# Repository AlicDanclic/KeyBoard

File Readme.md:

<center><h1>客制化键盘 -- 主键盘部分</h1></center>

<hr style="border: none; height: 2px; background: linear-gradient(to right, #ff0000, #ff7f00, #ffff00, #00ff00, #0000ff, #4b0082, #8f00ff); width: 100%; margin: 0 auto;">
<div style="text-align: center; font-family: 'Times New Roman', serif; margin: 20px auto; max-width: 800px;">
    <div style="margin: 20px 0;">
    	
    </div>
    <div style="font-weight: bold; font-size: 18px; color: #333; margin: 10px 0;">
    	Copyright Statement
    </div>
    <div style="font-size: 14px; color: #666; margin: 5px 0; font-family: 'SimSun', 'Times New Roman', serif;">
    	本文档/代码/作品受版权保护，版权所有@EternoPax。保留所有权利。
    </div>
    <div style="font-size: 14px; color: #666; margin: 5px 0; font-family: 'SimSun', 'Times New Roman', serif;">
        未经允许请勿转载<br>
        Do not reproduce without permission
    </div>
    <div style="font-size: 14px; color: #666; margin: 5px 0; font-family: 'SimSun', 'Times New Roman', serif;">
        联系我👉EternoPax@outlook.con
    </div>
    <div style="display: flex; align-items: center; justify-content: center; margin: 5px 0;">
        <span style="font-size: 14px; color: #666; font-family: 'SimSun', 'Times New Roman', serif; margin-right: 10px;">
            @Copyright EternoPax
        </span>
        
    </div>
</div>
<hr style="border: none; height: 2px; background: linear-gradient(to right, #ff0000, #ff7f00, #ffff00, #00ff00, #0000ff, #4b0082, #8f00ff); width: 100%; margin: 0 auto;">

> 作为一个客制化键盘的主键盘,在这里我将介绍我的学习过程,希望一起学习

### 基础介绍

作为一个客制化键盘来说,最基础的部分有外壳,PCB,定位板,键轴和键帽,而其他多大都是辅助使用,有了这些东西就基本可以做出来一个客制化键盘了。

### 键盘布局

> [Keyboard Layout Editor](https://www.keyboard-layout-editor.com/?ref=producthunt#/)

这是通过网站设计的键盘布局,虽然这个网站的功能很多,当实际上用不到,笔者就简单介绍一下个人常用的几个功能.

在PreSet里面是我们常见的键盘布局,个人比较喜欢在ANSI104全键盘的基础上进行删减.

在当你选中其中的一个按键,上边的DeleteKeys会亮起,你可以直接使用Delete进行删除,也可以左键选中按下Delete一起删除(注意:选中会出现一个框,只有完全在框里的按键会被选中)

选中按键后可以按下方向键来调整位置

在

在Raw data里面是我们键盘的布局格式,这个是我们以后用来绘制CAD的数据

在右上角可以看到Download,请你再绘制好之后务必下载JSON和SVG,其中JSON是为了方便以后再进行layout的修改,而SVG是为了之后的键帽设计做准备.

### 原理图绘制

### PCB绘制

### 键帽设计

### 3D外壳

### 固件编写

### 最终成果

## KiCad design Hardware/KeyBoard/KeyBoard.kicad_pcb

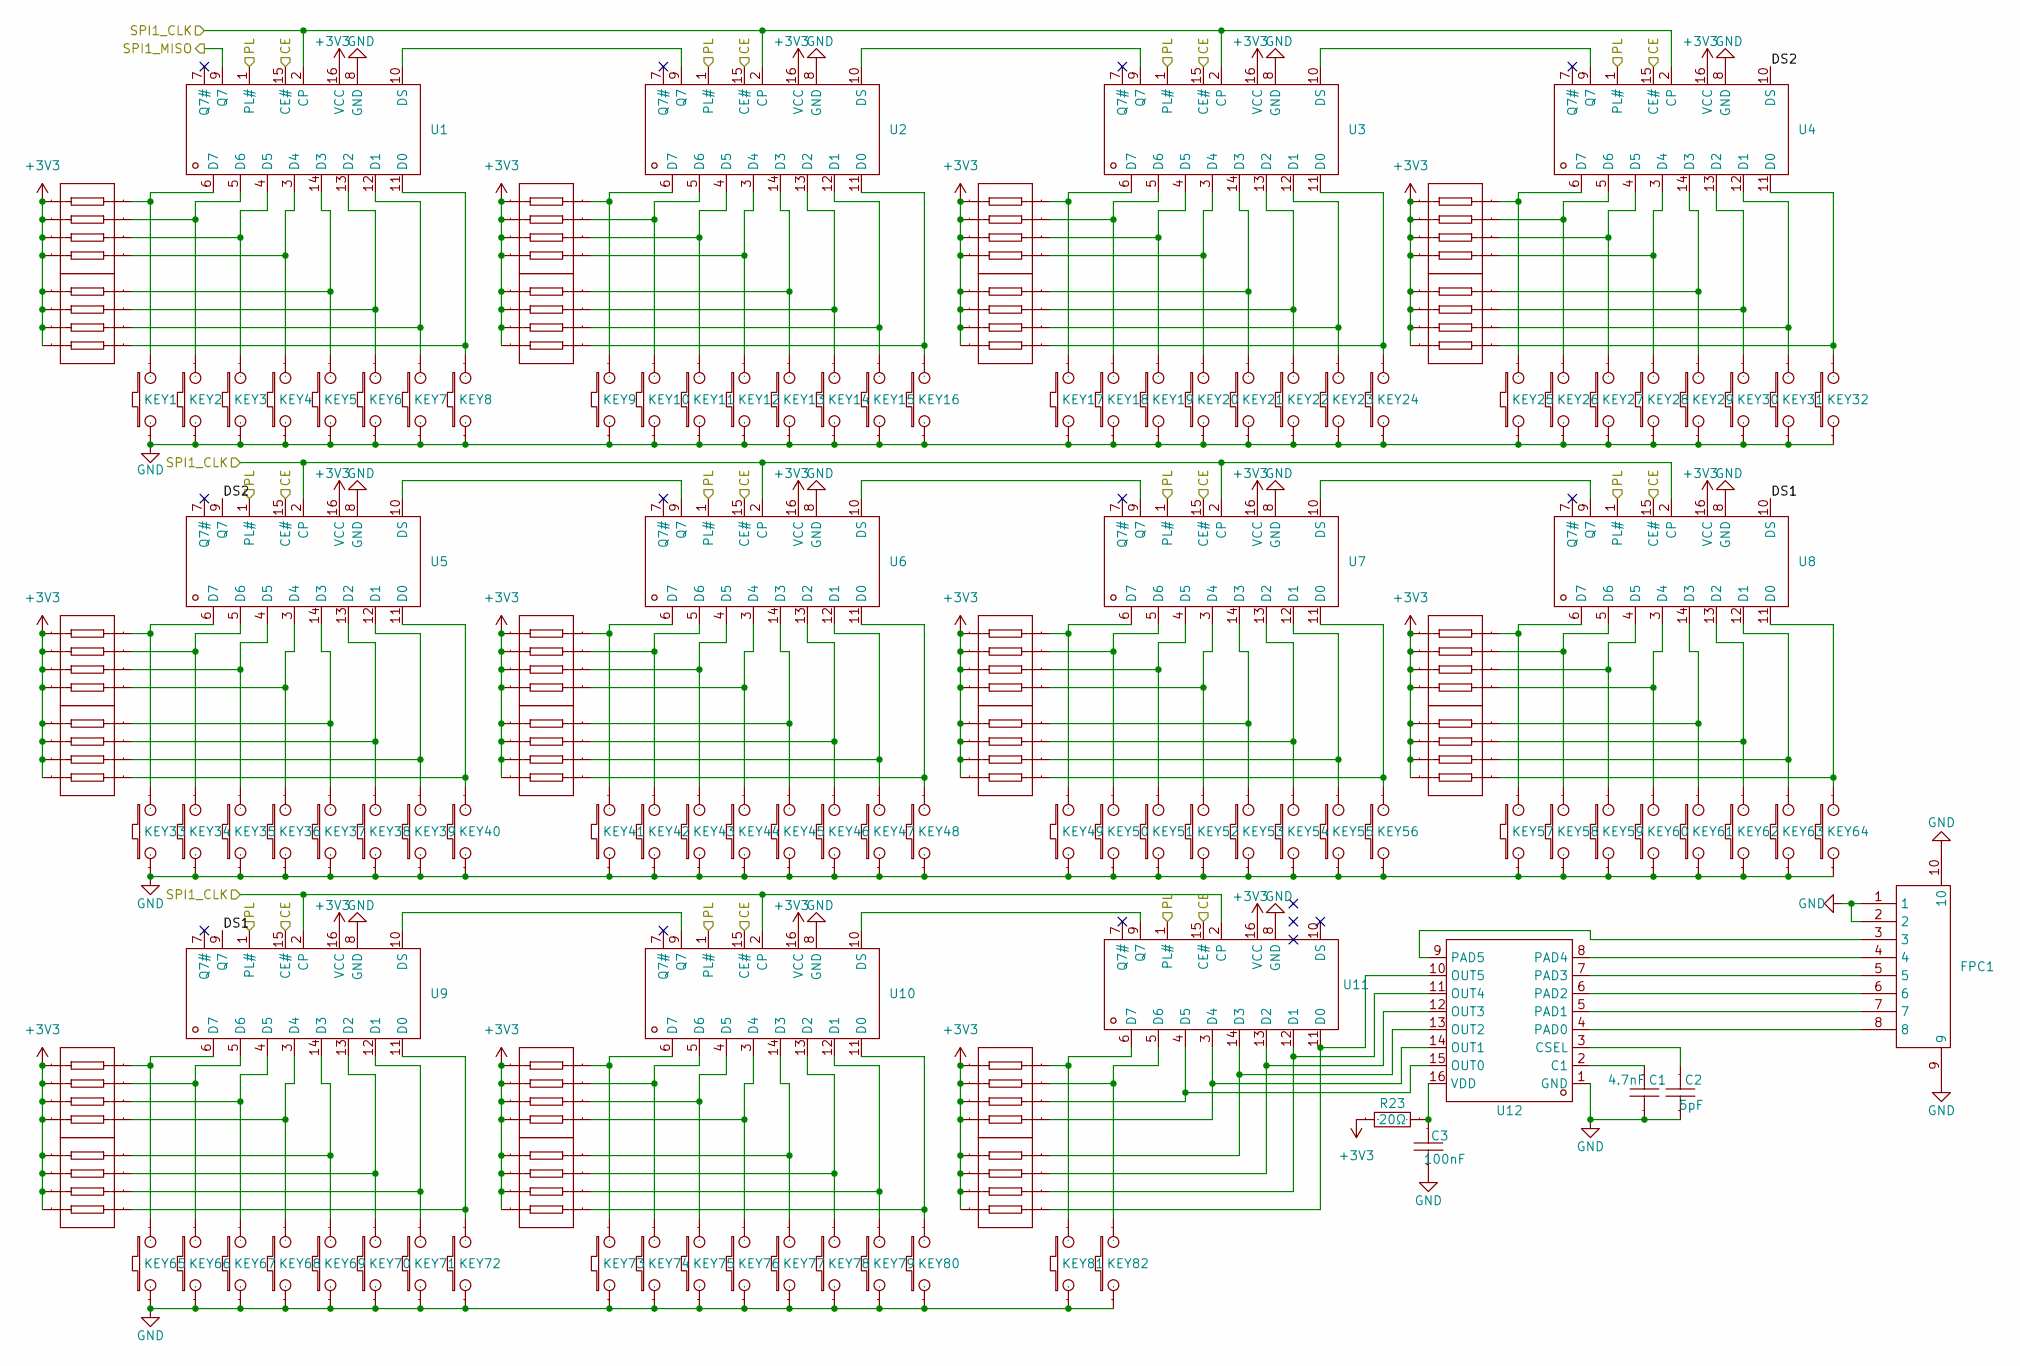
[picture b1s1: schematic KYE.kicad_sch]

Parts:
C1: 4.7nF; C0402; Manufacturer Part 0402B472K500NT; LCSC Part Name 4.7nF ±10% 50V
C2: 5pF; C0402; Manufacturer Part 0402B472K500NT; LCSC Part Name 4.7nF ±10% 50V
C3: 100nF; C0402; Manufacturer Part 0402B472K500NT; LCSC Part Name 4.7nF ±10% 50V
FPC1: FPC-SMD_P0.50-8P_FGS-XJ-H2.0; Manufacturer Part AFC01-S08FCA-00; LCSC Part Name 0.5mm P数:8 翻盖式 下接
KEY1, KEY2, KEY3, KEY4, KEY5, KEY6, KEY7, KEY8, KEY9, KEY10, KEY11, KEY12, KEY13, KEY14, KEY15, KEY16, KEY17, KEY18, KEY19, KEY20, KEY21, KEY22, KEY23, KEY24, KEY25, KEY26, KEY27, KEY28, KEY29, KEY30, KEY31, KEY32, KEY33, KEY34, KEY35, KEY36, KEY37, KEY38, KEY39, KEY40, KEY41, KEY42, KEY43, KEY44, KEY45, KEY46, KEY47, KEY48, KEY49, KEY50, KEY51, KEY52, KEY53, KEY54, KEY55, KEY56, KEY57, KEY58, KEY59, KEY60, KEY61, KEY62, KEY63, KEY64, KEY65, KEY66, KEY67, KEY68, KEY69, KEY70, KEY71, KEY72, KEY73, KEY74, KEY75, KEY76, KEY77, KEY78, KEY79, KEY80, KEY81, KEY82: MX-KEY-INSTALLED
R1, R2, R3, R4, R5, R6, R7, R8, R9, R10, R11, R12, R13, R14, R15, R16, R17, R18, R19, R20, R21, R22: 10kΩ; RES-ARRAY-SMD_0603-8P-L3.2-W1.6-BL; Manufacturer Part 4D03WGJ0103T5E; LCSC Part Name 10kΩ ±5%
R23: 20Ω; R0402; Manufacturer Part 0402WGF220JTCE; LCSC Part Name 22Ω ±1% 62.5mW
U1, U2, U3, U4, U5, U6, U7, U8, U9, U10, U11: SOIC-16_L9.9-W3.9-P1.27-LS6.0-BL; Manufacturer Part 74HC165D,653; LCSC Part Name 74HC165D,653
U12: SOP-16_L10.0-W3.9-P1.27-LS6.0-BL; Manufacturer Part XW06A; LCSC Part Name XW06A

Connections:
+3V3: R1.5, R1.6, R1.7, R1.8, R2.5, R2.6, R2.7, R2.8, R3.5, R3.6, R3.7, R3.8, R4.5, R4.6, R4.7, R4.8, R5.5, R5.6, R5.7, R5.8, R6.5, R6.6, R6.7, R6.8, R7.5, R7.6, R7.7, R7.8, R8.5, R8.6, R8.7, R8.8, R9.5, R9.6, R9.7, R9.8, R10.5, R10.6, R10.7, R10.8, R11.5, R11.6, R11.7, R11.8, R12.5, R12.6, R12.7, R12.8, R13.5, R13.6, R13.7, R13.8, R14.5, R14.6, R14.7, R14.8, R15.5, R15.6, R15.7, R15.8, R16.5, R16.6, R16.7, R16.8, R17.5, R17.6, R17.7, R17.8, R18.5, R18.6, R18.7, R18.8, R19.5, R19.6, R19.7, R19.8, R20.5, R20.6, R20.7, R20.8, R21.5, R21.6, R21.7, R21.8, R22.5, R22.6, R22.7, R22.8, R23.1, U1.16 (VCC), U2.16 (VCC), U3.16 (VCC), U4.16 (VCC), U5.16 (VCC), U6.16 (VCC), U7.16 (VCC), U8.16 (VCC), U9.16 (VCC), U10.16 (VCC), U11.16 (VCC); also elsewhere on the board
/KEY/CE: U1.15 (CE#), U2.15 (CE#), U3.15 (CE#), U4.15 (CE#), U5.15 (CE#), U6.15 (CE#), U7.15 (CE#), U8.15 (CE#), U9.15 (CE#), U10.15 (CE#), U11.15 (CE#); also elsewhere on the board
/KEY/DS1: U8.10 (DS), U9.9 (Q7)
/KEY/DS2: U4.10 (DS), U5.9 (Q7)
/KEY/PL: U1.1 (PL#), U2.1 (PL#), U3.1 (PL#), U4.1 (PL#), U5.1 (PL#), U6.1 (PL#), U7.1 (PL#), U8.1 (PL#), U9.1 (PL#), U10.1 (PL#), U11.1 (PL#); also elsewhere on the board
/KEY/SPI1_CLK: U1.2 (CP), U2.2 (CP), U3.2 (CP), U4.2 (CP), U5.2 (CP), U6.2 (CP), U7.2 (CP), U8.2 (CP), U9.2 (CP), U10.2 (CP), U11.2 (CP); also elsewhere on the board
/KEY/SPI1_MISO: U1.9 (Q7); also elsewhere on the board
GND: C1.2, C2.1, C3.1, FPC1.1, FPC1.2, FPC1.9, FPC1.10, KEY1.1, KEY2.1, KEY3.1, KEY4.1, KEY5.1, KEY6.1, KEY7.1, KEY8.1, KEY9.1, KEY10.1, KEY11.1, KEY12.1, KEY13.1, KEY14.1, KEY15.1, KEY16.1, KEY17.1, KEY18.1, KEY19.1, KEY20.1, KEY21.1, KEY22.1, KEY23.1, KEY24.1, KEY25.1, KEY26.1, KEY27.1, KEY28.1, KEY29.1, KEY30.1, KEY31.1, KEY32.1, KEY33.1, KEY34.1, KEY35.1, KEY36.1, KEY37.1, KEY38.1, KEY39.1, KEY40.1, KEY41.1, KEY42.1, KEY43.1, KEY44.1, KEY45.1, KEY46.1, KEY47.1, KEY48.1, KEY49.1, KEY50.1, KEY51.1, KEY52.1, KEY53.1, KEY54.1, KEY55.1, KEY56.1, KEY57.1, KEY58.1, KEY59.1, KEY60.1, KEY61.1, KEY62.1, KEY63.1, KEY64.1, KEY65.1, KEY66.1, KEY67.1, KEY68.1, KEY69.1, KEY70.1, KEY71.1, KEY72.1, KEY73.1, KEY74.1, KEY75.1, KEY76.1, KEY77.1, KEY78.1, KEY79.1, KEY80.1, KEY81.1, KEY82.1, U1.8 (GND), U2.8 (GND), U3.8 (GND), U4.8 (GND), U5.8 (GND), U6.8 (GND), U7.8 (GND), U8.8 (GND), U9.8 (GND), U10.8 (GND), U11.8 (GND), U12.1 (GND); also elsewhere on the board
unnamed: KEY8.2, R2.4, U1.11 (D0)
unnamed: KEY7.2, R2.3, U1.12 (D1)
unnamed: KEY6.2, R2.2, U1.13 (D2)
unnamed: KEY5.2, R2.1, U1.14 (D3)
unnamed: KEY4.2, R1.4, U1.3 (D4)
unnamed: KEY3.2, R1.3, U1.4 (D5)
unnamed: KEY2.2, R1.2, U1.5 (D6)
unnamed: KEY1.2, R1.1, U1.6 (D7)
unnamed: U1.10 (DS), U2.9 (Q7)
unnamed: KEY16.2, R4.4, U2.11 (D0)
unnamed: KEY15.2, R4.3, U2.12 (D1)
unnamed: KEY14.2, R4.2, U2.13 (D2)
unnamed: KEY13.2, R4.1, U2.14 (D3)
unnamed: KEY12.2, R3.4, U2.3 (D4)
unnamed: KEY11.2, R3.3, U2.4 (D5)
unnamed: KEY10.2, R3.2, U2.5 (D6)
unnamed: KEY9.2, R3.1, U2.6 (D7)
unnamed: U2.10 (DS), U3.9 (Q7)
unnamed: KEY24.2, R6.4, U3.11 (D0)
unnamed: KEY23.2, R6.3, U3.12 (D1)
unnamed: KEY22.2, R6.2, U3.13 (D2)
unnamed: KEY21.2, R6.1, U3.14 (D3)
unnamed: KEY20.2, R5.4, U3.3 (D4)
unnamed: KEY19.2, R5.3, U3.4 (D5)
unnamed: KEY18.2, R5.2, U3.5 (D6)
unnamed: KEY17.2, R5.1, U3.6 (D7)
unnamed: U3.10 (DS), U4.9 (Q7)
unnamed: KEY32.2, R8.4, U4.11 (D0)
unnamed: KEY31.2, R8.3, U4.12 (D1)
unnamed: KEY30.2, R8.2, U4.13 (D2)
unnamed: KEY29.2, R8.1, U4.14 (D3)
unnamed: KEY28.2, R7.4, U4.3 (D4)
unnamed: KEY27.2, R7.3, U4.4 (D5)
unnamed: KEY26.2, R7.2, U4.5 (D6)
unnamed: KEY25.2, R7.1, U4.6 (D7)
unnamed: KEY40.2, R10.4, U5.11 (D0)
unnamed: KEY39.2, R10.3, U5.12 (D1)
unnamed: KEY38.2, R10.2, U5.13 (D2)
unnamed: KEY37.2, R10.1, U5.14 (D3)
unnamed: KEY36.2, R9.4, U5.3 (D4)
unnamed: KEY35.2, R9.3, U5.4 (D5)
unnamed: KEY34.2, R9.2, U5.5 (D6)
unnamed: KEY33.2, R9.1, U5.6 (D7)
unnamed: U5.10 (DS), U6.9 (Q7)
unnamed: KEY48.2, R12.4, U6.11 (D0)
unnamed: KEY47.2, R12.3, U6.12 (D1)
unnamed: KEY46.2, R12.2, U6.13 (D2)
unnamed: KEY45.2, R12.1, U6.14 (D3)
unnamed: KEY44.2, R11.4, U6.3 (D4)
unnamed: KEY43.2, R11.3, U6.4 (D5)
unnamed: KEY42.2, R11.2, U6.5 (D6)
unnamed: KEY41.2, R11.1, U6.6 (D7)
unnamed: U6.10 (DS), U7.9 (Q7)
unnamed: KEY56.2, R14.4, U7.11 (D0)
unnamed: KEY55.2, R14.3, U7.12 (D1)
unnamed: KEY54.2, R14.2, U7.13 (D2)
unnamed: KEY53.2, R14.1, U7.14 (D3)
unnamed: KEY52.2, R13.4, U7.3 (D4)
unnamed: KEY51.2, R13.3, U7.4 (D5)
unnamed: KEY50.2, R13.2, U7.5 (D6)
unnamed: KEY49.2, R13.1, U7.6 (D7)
unnamed: U7.10 (DS), U8.9 (Q7)
unnamed: KEY64.2, R16.4, U8.11 (D0)
unnamed: KEY63.2, R16.3, U8.12 (D1)
unnamed: KEY62.2, R16.2, U8.13 (D2)
unnamed: KEY61.2, R16.1, U8.14 (D3)
unnamed: KEY60.2, R15.4, U8.3 (D4)
unnamed: KEY59.2, R15.3, U8.4 (D5)
unnamed: KEY58.2, R15.2, U8.5 (D6)
unnamed: KEY57.2, R15.1, U8.6 (D7)
unnamed: KEY72.2, R18.4, U9.11 (D0)
unnamed: KEY71.2, R18.3, U9.12 (D1)
unnamed: KEY70.2, R18.2, U9.13 (D2)
unnamed: KEY69.2, R18.1, U9.14 (D3)
unnamed: KEY68.2, R17.4, U9.3 (D4)
unnamed: KEY67.2, R17.3, U9.4 (D5)
unnamed: KEY66.2, R17.2, U9.5 (D6)
unnamed: KEY65.2, R17.1, U9.6 (D7)
unnamed: KEY80.2, R20.4, U10.11 (D0)
unnamed: KEY79.2, R20.3, U10.12 (D1)
unnamed: KEY78.2, R20.2, U10.13 (D2)
unnamed: KEY77.2, R20.1, U10.14 (D3)
unnamed: KEY76.2, R19.4, U10.3 (D4)
unnamed: KEY75.2, R19.3, U10.4 (D5)
unnamed: KEY74.2, R19.2, U10.5 (D6)
unnamed: KEY73.2, R19.1, U10.6 (D7)
unnamed: U10.10 (DS), U11.9 (Q7)
unnamed: U9.10 (DS), U10.9 (Q7)
unnamed: R22.4, U11.11 (D0), U12.10 (OUT5)
unnamed: R22.3, U11.12 (D1), U12.11 (OUT4)
unnamed: R22.2, U11.13 (D2), U12.12 (OUT3)
unnamed: R22.1, U11.14 (D3), U12.13 (OUT2)
unnamed: R21.4, U11.3 (D4), U12.14 (OUT1)
unnamed: R21.3, U11.4 (D5), U12.15 (OUT0)
unnamed: KEY82.2, R21.2, U11.5 (D6)
unnamed: KEY81.2, R21.1, U11.6 (D7)
unnamed: C1.1, U12.2 (C1)
unnamed: C2.2, U12.3 (CSEL)
unnamed: FPC1.8, U12.4 (PAD0)
unnamed: FPC1.7, U12.5 (PAD1)
unnamed: FPC1.6, U12.6 (PAD2)
unnamed: FPC1.5, U12.7 (PAD3)
unnamed: FPC1.4, U12.8 (PAD4)
unnamed: FPC1.3, U12.9 (PAD5)
unnamed: C3.2, R23.2, U12.16 (VDD)

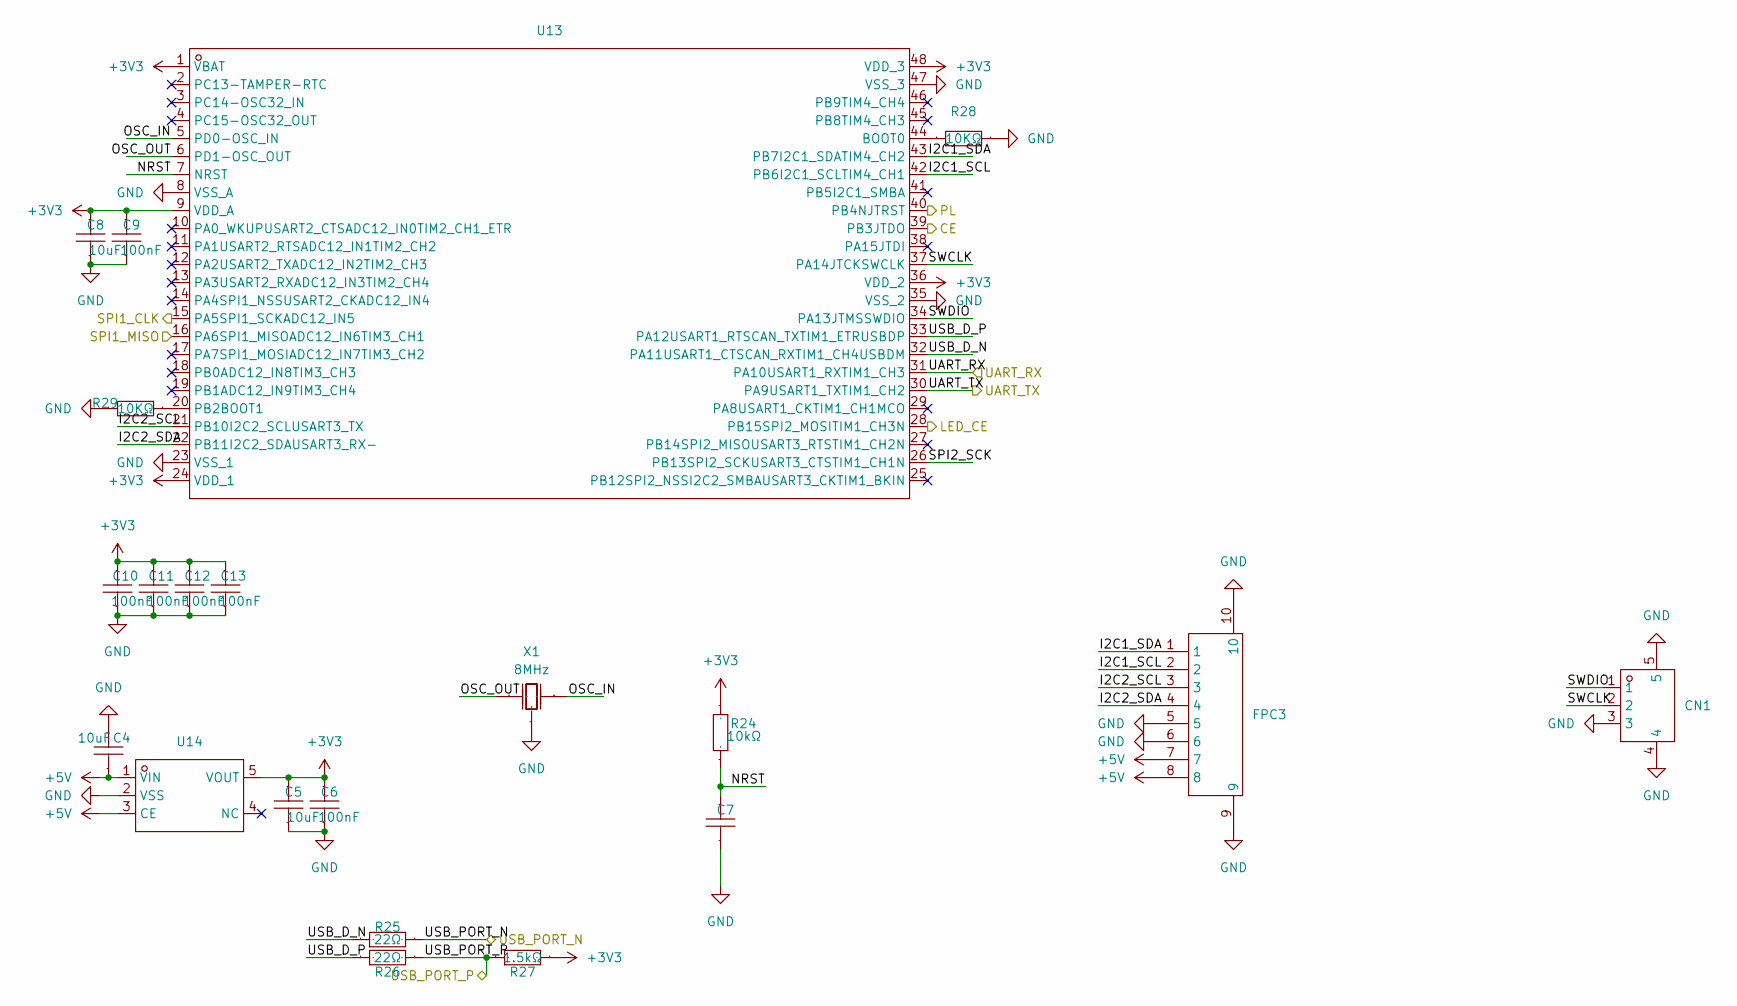
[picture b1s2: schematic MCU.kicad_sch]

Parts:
C4, C5, C8: 10uF; C0402; Manufacturer Part 0402B472K500NT; LCSC Part Name 4.7nF ±10% 50V
C6, C7, C9, C10, C11, C12, C13: 100nF; C0402; Manufacturer Part 0402B472K500NT; LCSC Part Name 4.7nF ±10% 50V
CN1: CONN-TH_3P-P1.25_GH1.25; Manufacturer Part WAFER-GH1.25-3PWB; LCSC Part Name 1x3P 间距:1.25mm 卧贴 系列:GH
FPC3: FPC-SMD_P0.50-8P_FGS-XJ-H2.0; Manufacturer Part AFC01-S08FCA-00; LCSC Part Name 0.5mm P数:8 翻盖式 下接
R24: 10kΩ; R0402; Manufacturer Part 0402WGF220JTCE; LCSC Part Name 22Ω ±1% 62.5mW
R25, R26: 22Ω; R0402; Manufacturer Part 0402WGF220JTCE; LCSC Part Name 22Ω ±1% 62.5mW
R27: 1.5kΩ; R0402; Manufacturer Part 0402WGF220JTCE; LCSC Part Name 22Ω ±1% 62.5mW
R28, R29: 10KΩ; R0402; Manufacturer Part 0402WGF220JTCE; LCSC Part Name 22Ω ±1% 62.5mW
U13: LQFP-48_L7.0-W7.0-P0.50-LS9.0-BL; Manufacturer Part STM32F103CBT6; LCSC Part Name STM32F103CBT6
U14: SOT-25_L3.0-W1.6-P0.95-LS2.8-BL; Manufacturer Part XC6210B332MR; LCSC Part Name Vin=6V Vout=3.3V 900mA 60dB@(1kHz)
X1: 8MHz; OSC-SMD_3P-L3.2-W1.3-P1.20; Manufacturer Part CSTNE8M00GH5C000R0; LCSC Part Name 8MHz ±0.07% 33pF

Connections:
+3V3: C5.1, C6.1, C8.1, C9.1, C10.1, C11.1, C12.1, C13.1, R24.2, R27.2, U13.1 (VBAT), U13.9 (VDD_A), U13.24 (VDD_1), U13.36 (VDD_2), U13.48 (VDD_3), U14.5 (VOUT); also elsewhere on the board
+5V: C4.1, FPC3.7, FPC3.8, U14.1 (VIN), U14.3 (CE); also elsewhere on the board
/Device/USB_1_DN: R25.2; also elsewhere on the board
/Device/USB_1_DP: R26.2, R27.1; also elsewhere on the board
/KEY/CE: U13.39 (PB3JTDO); also elsewhere on the board
/KEY/PL: U13.40 (PB4NJTRST); also elsewhere on the board
/KEY/SPI1_CLK: U13.15 (PA5SPI1_SCKADC12_IN5); also elsewhere on the board
/KEY/SPI1_MISO: U13.16 (PA6SPI1_MISOADC12_IN6TIM3_CH1); also elsewhere on the board
/LED/LED_CE: U13.28 (PB15SPI2_MOSITIM1_CH3N); also elsewhere on the board
/MCU/I2C1_SCL: FPC3.2, U13.42 (PB6I2C1_SCLTIM4_CH1)
/MCU/I2C1_SDA: FPC3.1, U13.43 (PB7I2C1_SDATIM4_CH2)
/MCU/I2C2_SCL: FPC3.3, U13.21 (PB10I2C2_SCLUSART3_TX)
/MCU/I2C2_SDA: FPC3.4, U13.22 (PB11I2C2_SDAUSART3_RX-)
/MCU/NRST: C7.1, R24.1, U13.7 (NRST)
/MCU/OSC_IN: U13.5 (PD0-OSC_IN), X1.1 (OSC1)
/MCU/OSC_OUT: U13.6 (PD1-OSC_OUT), X1.3 (OSC2)
/MCU/SPI2_SCK: U13.26 (PB13SPI2_SCKUSART3_CTSTIM1_CH1N)
/MCU/SWCLK: CN1.2, U13.37 (PA14JTCKSWCLK)
/MCU/SWDIO: CN1.1, U13.34 (PA13JTMSSWDIO)
/MCU/UART_RX: U13.31 (PA10USART1_RXTIM1_CH3); also elsewhere on the board
/MCU/UART_TX: U13.30 (PA9USART1_TXTIM1_CH2); also elsewhere on the board
/MCU/USB_D_N: R25.1, U13.32 (PA11USART1_CTSCAN_RXTIM1_CH4USBDM)
/MCU/USB_D_P: R26.1, U13.33 (PA12USART1_RTSCAN_TXTIM1_ETRUSBDP)
GND: C4.2, C5.2, C6.2, C7.2, C8.2, C9.2, C10.2, C11.2, C12.2, C13.2, CN1.3, CN1.4, CN1.5, FPC3.5, FPC3.6, FPC3.9, FPC3.10, R28.2, R29.2, U13.8 (VSS_A), U13.23 (VSS_1), U13.35 (VSS_2), U13.47 (VSS_3), U14.2 (VSS), X1.2 (GND); also elsewhere on the board
unnamed: R28.1, U13.44 (BOOT0)
unnamed: R29.1, U13.20 (PB2BOOT1)

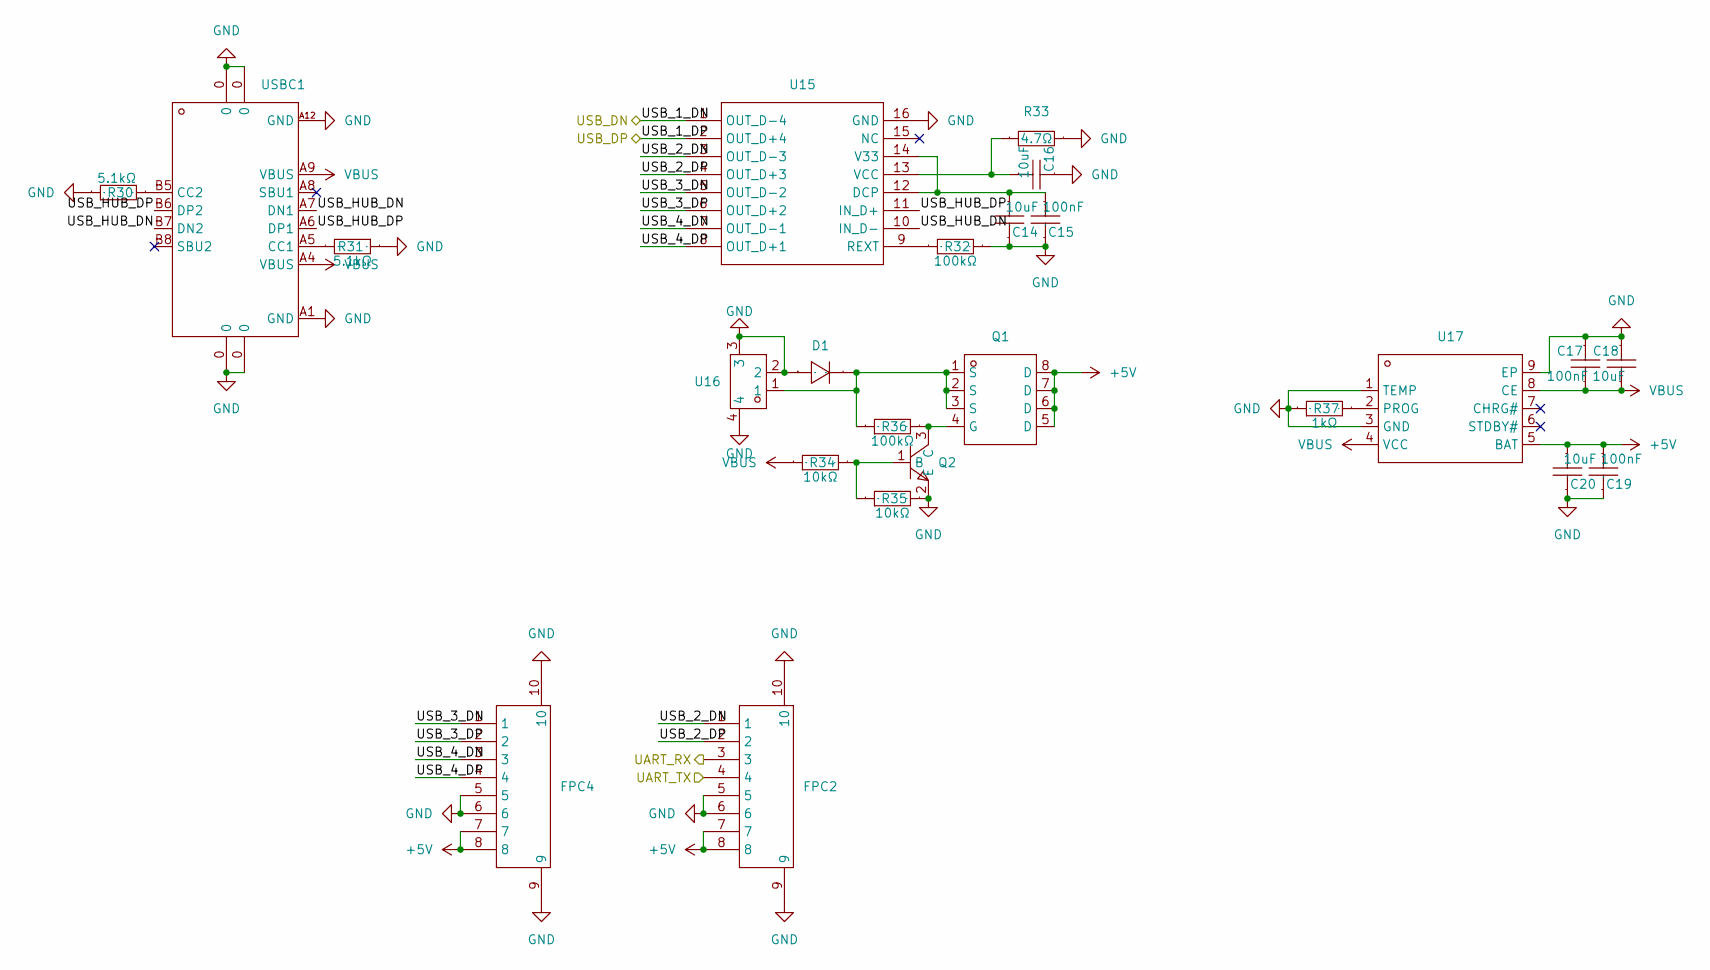
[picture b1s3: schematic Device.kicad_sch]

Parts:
C14, C16, C18, C20: 10uF; C0402; Manufacturer Part 0402B472K500NT; LCSC Part Name 4.7nF ±10% 50V
C15, C17, C19: 100nF; C0402; Manufacturer Part 0402B472K500NT; LCSC Part Name 4.7nF ±10% 50V
D1: SOD-523_L1.2-W0.8-LS1.6-FD; Manufacturer Part B5819WS; LCSC Part Name 40V 1A 900mV@3A
FPC2, FPC4: FPC-SMD_P0.50-8P_FGS-XJ-H2.0; Manufacturer Part AFC01-S08FCA-00; LCSC Part Name 0.5mm P数:8 翻盖式 下接
Q1: POWERTDFN-8_L3.1-W3.1-P0.65-LS3.3-BL; Manufacturer Part EMB12P03V; LCSC Part Name P沟道 30V 21A
Q2: SOT-23-3_L2.9-W1.3-P1.90-LS2.4-BR; Manufacturer Part S8050 J3Y; LCSC Part Name S8050
R30, R31: 5.1kΩ; R0402; Manufacturer Part 0402WGF220JTCE; LCSC Part Name 22Ω ±1% 62.5mW
R32, R36: 100kΩ; R0402; Manufacturer Part 0402WGF220JTCE; LCSC Part Name 22Ω ±1% 62.5mW
R33: 4.7Ω; R0402; Manufacturer Part 0402WGF220JTCE; LCSC Part Name 22Ω ±1% 62.5mW
R34, R35: 10kΩ; R0402; Manufacturer Part 0402WGF220JTCE; LCSC Part Name 22Ω ±1% 62.5mW
R37: 1kΩ; R0402; Manufacturer Part 0402WGF220JTCE; LCSC Part Name 22Ω ±1% 62.5mW
U15: SOP-16
U16: CONN-SMD_2P-P2.50_HCTL_HC-XH-2ALT; Manufacturer Part ZX-XH2.54-2PLT; LCSC Part Name XH 2.54mm 1x2P 立贴
U17: ESOP-8_L4.9-W3.9-P1.27-LS6.0-BL-EP; Manufacturer Part TP4056; LCSC Part Name 1A鋰電池充電IC
USBC1: USB-C-SMD_TYPE-C-USB-17; Manufacturer Part 918-418K2023S40001; LCSC Part Name Type-C 母座

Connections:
+5V: C19.2, C20.1, FPC2.7, FPC2.8, FPC4.7, FPC4.8, Q1.5 (D), Q1.6 (D), Q1.7 (D), Q1.8 (D), U17.5 (BAT); also elsewhere on the board
/Device/USB_1_DN: U15.1 (OUT_D-4); also elsewhere on the board
/Device/USB_1_DP: U15.2 (OUT_D+4); also elsewhere on the board
/Device/USB_2_DN: FPC2.1, U15.3 (OUT_D-3)
/Device/USB_2_DP: FPC2.2, U15.4 (OUT_D+3)
/Device/USB_3_DN: FPC4.1, U15.5 (OUT_D-2)
/Device/USB_3_DP: FPC4.2, U15.6 (OUT_D+2)
/Device/USB_4_DN: FPC4.3, U15.7 (OUT_D-1)
/Device/USB_4_DP: FPC4.4, U15.8 (OUT_D+1)
/Device/USB_HUB_DN: U15.10 (IN_D-), USBC1.A7 (DN1), USBC1.B7 (DN2)
/Device/USB_HUB_DP: U15.11 (IN_D+), USBC1.A6 (DP1), USBC1.B6 (DP2)
/MCU/UART_RX: FPC2.3; also elsewhere on the board
/MCU/UART_TX: FPC2.4; also elsewhere on the board
GND: C14.2, C15.1, C16.2, C17.1, C18.2, C19.1, C20.2, D1.1 (A), FPC2.5, FPC2.6, FPC2.9, FPC2.10, FPC4.5, FPC4.6, FPC4.9, FPC4.10, Q2.2 (E), R30.1, R31.1, R32.2, R33.2, R35.2, R37.1, U15.16 (GND), U16.2, U16.3, U16.4, U17.1 (TEMP), U17.3 (GND), U17.9 (EP), USBC1.0, USBC1.A1 (GND), USBC1.A12 (GND); also elsewhere on the board
unnamed: D1.2 (K), Q1.1 (S), Q1.2 (S), Q1.3 (S), R36.1, U16.1
unnamed: Q1.4 (G), Q2.3 (C), R36.2
unnamed: Q2.1 (B), R34.2, R35.1
unnamed: C14.1, C15.2, U15.12 (DCP), U15.14 (V33)
unnamed: R32.1, U15.9 (REXT)
unnamed: C16.1, R33.1, U15.13 (VCC)
unnamed: R37.2, U17.2 (PROG)
unnamed: R31.2, USBC1.A5 (CC1)
unnamed: R30.2, USBC1.B5 (CC2)
VBUS: C17.2, C18.1, R34.1, U17.4 (VCC), U17.8 (CE), USBC1.A4 (VBUS), USBC1.A9 (VBUS)

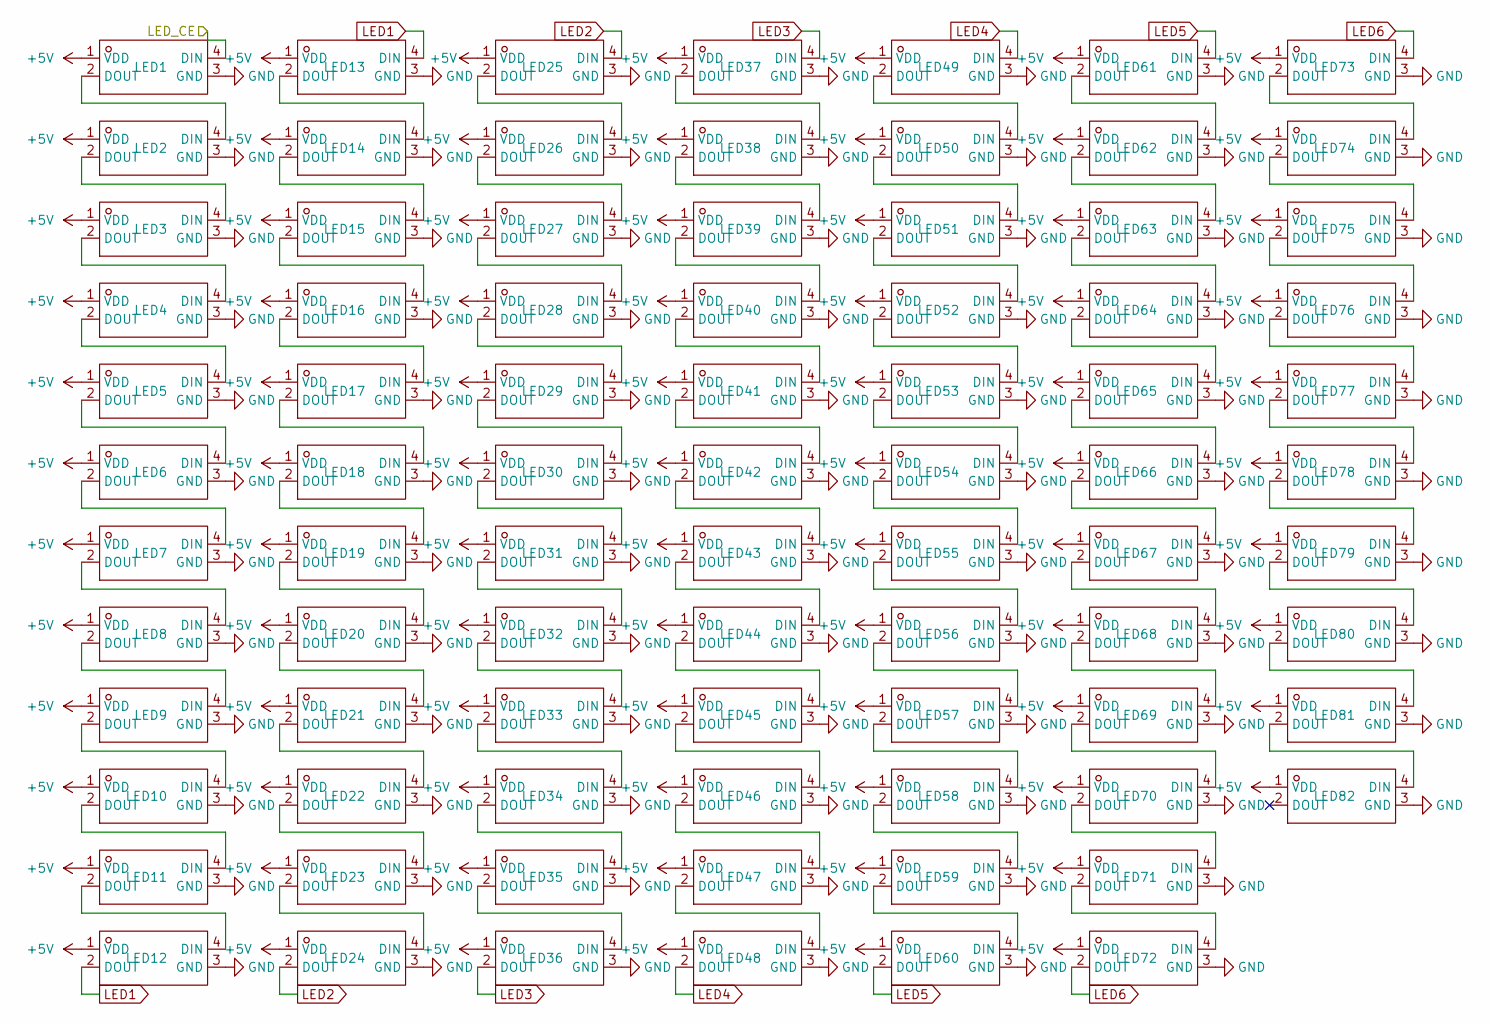
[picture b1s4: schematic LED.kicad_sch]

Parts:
LED1, LED2, LED3, LED4, LED5, LED6, LED7, LED8, LED9, LED10, LED11, LED12, LED13, LED14, LED15, LED16, LED17, LED18, LED19, LED20, LED21, LED22, LED23, LED24, LED25, LED26, LED27, LED28, LED29, LED30, LED31, LED32, LED33, LED34, LED35, LED36, LED37, LED38, LED39, LED40, LED41, LED42, LED43, LED44, LED45, LED46, LED47, LED48, LED49, LED50, LED51, LED52, LED53, LED54, LED55, LED56, LED57, LED58, LED59, LED60, LED61, LED62, LED63, LED64, LED65, LED66, LED67, LED68, LED69, LED70, LED71, LED72, LED73, LED74, LED75, LED76, LED77, LED78, LED79, LED80, LED81, LED82: LED-SMD_L3.2-W2.8_YO-WS2812B-3528; Manufacturer Part Yo-WS2812B-3528反贴雾状

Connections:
+5V: LED1.1 (VDD), LED2.1 (VDD), LED3.1 (VDD), LED4.1 (VDD), LED5.1 (VDD), LED6.1 (VDD), LED7.1 (VDD), LED8.1 (VDD), LED9.1 (VDD), LED10.1 (VDD), LED11.1 (VDD), LED12.1 (VDD), LED13.1 (VDD), LED14.1 (VDD), LED15.1 (VDD), LED16.1 (VDD), LED17.1 (VDD), LED18.1 (VDD), LED19.1 (VDD), LED20.1 (VDD), LED21.1 (VDD), LED22.1 (VDD), LED23.1 (VDD), LED24.1 (VDD), LED25.1 (VDD), LED26.1 (VDD), LED27.1 (VDD), LED28.1 (VDD), LED29.1 (VDD), LED30.1 (VDD), LED31.1 (VDD), LED32.1 (VDD), LED33.1 (VDD), LED34.1 (VDD), LED35.1 (VDD), LED36.1 (VDD), LED37.1 (VDD), LED38.1 (VDD), LED39.1 (VDD), LED40.1 (VDD), LED41.1 (VDD), LED42.1 (VDD), LED43.1 (VDD), LED44.1 (VDD), LED45.1 (VDD), LED46.1 (VDD), LED47.1 (VDD), LED48.1 (VDD), LED49.1 (VDD), LED50.1 (VDD), LED51.1 (VDD), LED52.1 (VDD), LED53.1 (VDD), LED54.1 (VDD), LED55.1 (VDD), LED56.1 (VDD), LED57.1 (VDD), LED58.1 (VDD), LED59.1 (VDD), LED60.1 (VDD), LED61.1 (VDD), LED62.1 (VDD), LED63.1 (VDD), LED64.1 (VDD), LED65.1 (VDD), LED66.1 (VDD), LED67.1 (VDD), LED68.1 (VDD), LED69.1 (VDD), LED70.1 (VDD), LED71.1 (VDD), LED72.1 (VDD), LED73.1 (VDD), LED74.1 (VDD), LED75.1 (VDD), LED76.1 (VDD), LED77.1 (VDD), LED78.1 (VDD), LED79.1 (VDD), LED80.1 (VDD), LED81.1 (VDD), LED82.1 (VDD); also elsewhere on the board
/LED/LED_CE: LED1.4 (DIN); also elsewhere on the board
GND: LED1.3 (GND), LED2.3 (GND), LED3.3 (GND), LED4.3 (GND), LED5.3 (GND), LED6.3 (GND), LED7.3 (GND), LED8.3 (GND), LED9.3 (GND), LED10.3 (GND), LED11.3 (GND), LED12.3 (GND), LED13.3 (GND), LED14.3 (GND), LED15.3 (GND), LED16.3 (GND), LED17.3 (GND), LED18.3 (GND), LED19.3 (GND), LED20.3 (GND), LED21.3 (GND), LED22.3 (GND), LED23.3 (GND), LED24.3 (GND), LED25.3 (GND), LED26.3 (GND), LED27.3 (GND), LED28.3 (GND), LED29.3 (GND), LED30.3 (GND), LED31.3 (GND), LED32.3 (GND), LED33.3 (GND), LED34.3 (GND), LED35.3 (GND), LED36.3 (GND), LED37.3 (GND), LED38.3 (GND), LED39.3 (GND), LED40.3 (GND), LED41.3 (GND), LED42.3 (GND), LED43.3 (GND), LED44.3 (GND), LED45.3 (GND), LED46.3 (GND), LED47.3 (GND), LED48.3 (GND), LED49.3 (GND), LED50.3 (GND), LED51.3 (GND), LED52.3 (GND), LED53.3 (GND), LED54.3 (GND), LED55.3 (GND), LED56.3 (GND), LED57.3 (GND), LED58.3 (GND), LED59.3 (GND), LED60.3 (GND), LED61.3 (GND), LED62.3 (GND), LED63.3 (GND), LED64.3 (GND), LED65.3 (GND), LED66.3 (GND), LED67.3 (GND), LED68.3 (GND), LED69.3 (GND), LED70.3 (GND), LED71.3 (GND), LED72.3 (GND), LED73.3 (GND), LED74.3 (GND), LED75.3 (GND), LED76.3 (GND), LED77.3 (GND), LED78.3 (GND), LED79.3 (GND), LED80.3 (GND), LED81.3 (GND), LED82.3 (GND); also elsewhere on the board
LED1: LED12.2 (DOUT), LED13.4 (DIN)
LED2: LED24.2 (DOUT), LED25.4 (DIN)
LED3: LED36.2 (DOUT), LED37.4 (DIN)
LED4: LED48.2 (DOUT), LED49.4 (DIN)
LED5: LED60.2 (DOUT), LED61.4 (DIN)
LED6: LED72.2 (DOUT), LED73.4 (DIN)
unnamed: LED1.2 (DOUT), LED2.4 (DIN)
unnamed: LED2.2 (DOUT), LED3.4 (DIN)
unnamed: LED3.2 (DOUT), LED4.4 (DIN)
unnamed: LED4.2 (DOUT), LED5.4 (DIN)
unnamed: LED5.2 (DOUT), LED6.4 (DIN)
unnamed: LED6.2 (DOUT), LED7.4 (DIN)
unnamed: LED7.2 (DOUT), LED8.4 (DIN)
unnamed: LED8.2 (DOUT), LED9.4 (DIN)
unnamed: LED9.2 (DOUT), LED10.4 (DIN)
unnamed: LED10.2 (DOUT), LED11.4 (DIN)
unnamed: LED11.2 (DOUT), LED12.4 (DIN)
unnamed: LED13.2 (DOUT), LED14.4 (DIN)
unnamed: LED14.2 (DOUT), LED15.4 (DIN)
unnamed: LED15.2 (DOUT), LED16.4 (DIN)
unnamed: LED16.2 (DOUT), LED17.4 (DIN)
unnamed: LED17.2 (DOUT), LED18.4 (DIN)
unnamed: LED18.2 (DOUT), LED19.4 (DIN)
unnamed: LED19.2 (DOUT), LED20.4 (DIN)
unnamed: LED20.2 (DOUT), LED21.4 (DIN)
unnamed: LED21.2 (DOUT), LED22.4 (DIN)
unnamed: LED22.2 (DOUT), LED23.4 (DIN)
unnamed: LED23.2 (DOUT), LED24.4 (DIN)
unnamed: LED25.2 (DOUT), LED26.4 (DIN)
unnamed: LED26.2 (DOUT), LED27.4 (DIN)
unnamed: LED27.2 (DOUT), LED28.4 (DIN)
unnamed: LED28.2 (DOUT), LED29.4 (DIN)
unnamed: LED29.2 (DOUT), LED30.4 (DIN)
unnamed: LED30.2 (DOUT), LED31.4 (DIN)
unnamed: LED31.2 (DOUT), LED32.4 (DIN)
unnamed: LED32.2 (DOUT), LED33.4 (DIN)
unnamed: LED33.2 (DOUT), LED34.4 (DIN)
unnamed: LED34.2 (DOUT), LED35.4 (DIN)
unnamed: LED35.2 (DOUT), LED36.4 (DIN)
unnamed: LED37.2 (DOUT), LED38.4 (DIN)
unnamed: LED38.2 (DOUT), LED39.4 (DIN)
unnamed: LED39.2 (DOUT), LED40.4 (DIN)
unnamed: LED40.2 (DOUT), LED41.4 (DIN)
unnamed: LED41.2 (DOUT), LED42.4 (DIN)
unnamed: LED42.2 (DOUT), LED43.4 (DIN)
unnamed: LED43.2 (DOUT), LED44.4 (DIN)
unnamed: LED44.2 (DOUT), LED45.4 (DIN)
unnamed: LED45.2 (DOUT), LED46.4 (DIN)
unnamed: LED46.2 (DOUT), LED47.4 (DIN)
unnamed: LED47.2 (DOUT), LED48.4 (DIN)
unnamed: LED49.2 (DOUT), LED50.4 (DIN)
unnamed: LED50.2 (DOUT), LED51.4 (DIN)
unnamed: LED51.2 (DOUT), LED52.4 (DIN)
unnamed: LED52.2 (DOUT), LED53.4 (DIN)
unnamed: LED53.2 (DOUT), LED54.4 (DIN)
unnamed: LED54.2 (DOUT), LED55.4 (DIN)
unnamed: LED55.2 (DOUT), LED56.4 (DIN)
unnamed: LED56.2 (DOUT), LED57.4 (DIN)
unnamed: LED57.2 (DOUT), LED58.4 (DIN)
unnamed: LED58.2 (DOUT), LED59.4 (DIN)
unnamed: LED59.2 (DOUT), LED60.4 (DIN)
unnamed: LED61.2 (DOUT), LED62.4 (DIN)
unnamed: LED62.2 (DOUT), LED63.4 (DIN)
unnamed: LED63.2 (DOUT), LED64.4 (DIN)
unnamed: LED64.2 (DOUT), LED65.4 (DIN)
unnamed: LED65.2 (DOUT), LED66.4 (DIN)
unnamed: LED66.2 (DOUT), LED67.4 (DIN)
unnamed: LED67.2 (DOUT), LED68.4 (DIN)
unnamed: LED68.2 (DOUT), LED69.4 (DIN)
unnamed: LED69.2 (DOUT), LED70.4 (DIN)
unnamed: LED70.2 (DOUT), LED71.4 (DIN)
unnamed: LED71.2 (DOUT), LED72.4 (DIN)
unnamed: LED73.2 (DOUT), LED74.4 (DIN)
unnamed: LED74.2 (DOUT), LED75.4 (DIN)
unnamed: LED75.2 (DOUT), LED76.4 (DIN)
unnamed: LED76.2 (DOUT), LED77.4 (DIN)
unnamed: LED77.2 (DOUT), LED78.4 (DIN)
unnamed: LED78.2 (DOUT), LED79.4 (DIN)
unnamed: LED79.2 (DOUT), LED80.4 (DIN)
unnamed: LED80.2 (DOUT), LED81.4 (DIN)
unnamed: LED81.2 (DOUT), LED82.4 (DIN)

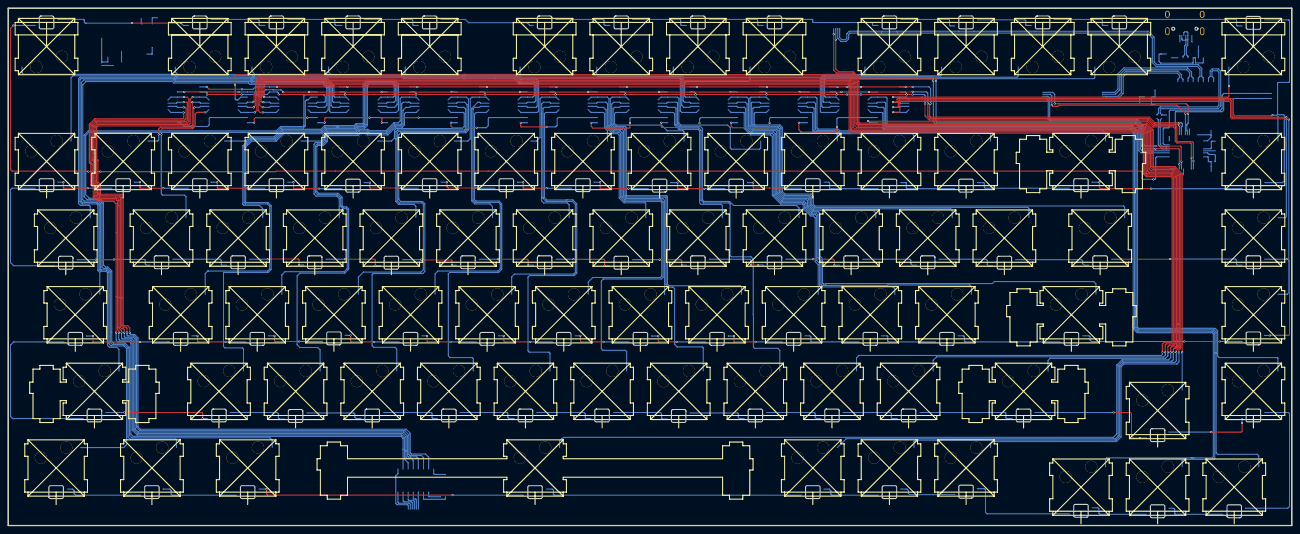
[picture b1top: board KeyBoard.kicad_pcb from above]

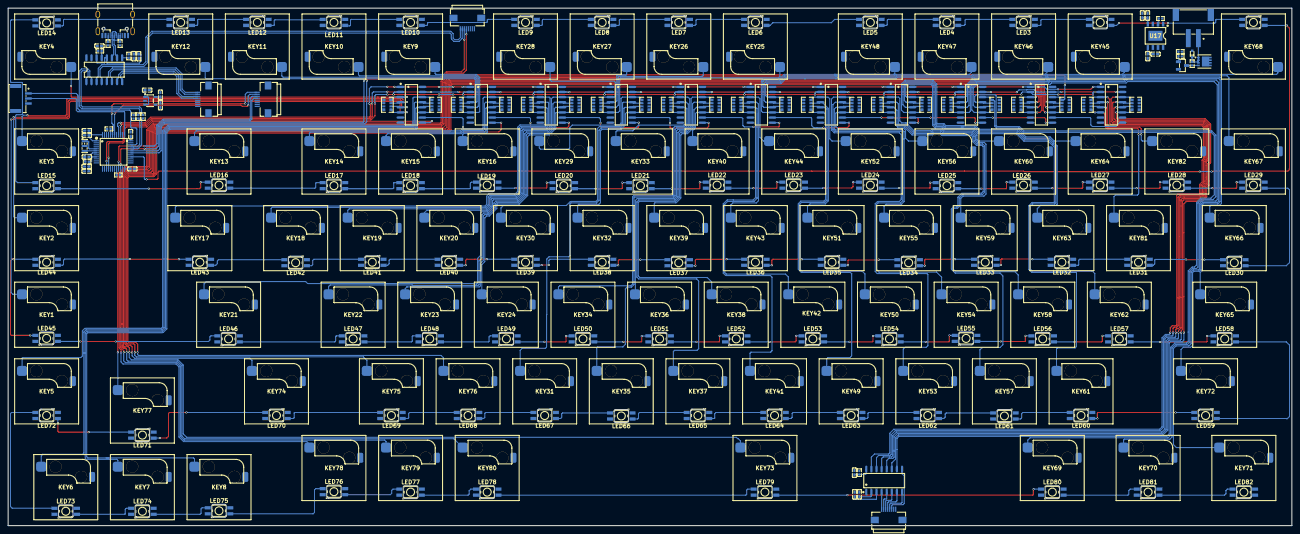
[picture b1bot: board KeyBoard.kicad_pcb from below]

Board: 2 copper layers, 319.1 x 128.7 mm, 248 parts (248 on the bottom side), 231 nets.

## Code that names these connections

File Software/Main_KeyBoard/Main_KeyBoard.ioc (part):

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Mcu.Name=STM32F103C(8-B)Tx
Mcu.Package=LQFP48
Mcu.UserName=STM32F103CBTx
PA10.Mode=Asynchronous
PA10.Signal=USART1_RX
PA11.Mode=Device
PA11.Signal=USB_DM
PA12.Mode=Device
PA12.Signal=USB_DP
PA13.Mode=Serial_Wire
PA13.Signal=SYS_JTMS-SWDIO
PA14.Mode=Serial_Wire
PA14.Signal=SYS_JTCK-SWCLK
PA5.Mode=RX_Only_Simplex_Unidirect_Master
PA5.Signal=SPI1_SCK
PA6.Mode=RX_Only_Simplex_Unidirect_Master
PA6.Signal=SPI1_MISO
PA9.Mode=Asynchronous
PA9.Signal=USART1_TX
PB10.Mode=I2C
PB10.Signal=I2C2_SCL
PB11.Mode=I2C
PB11.Signal=I2C2_SDA
PB13.Mode=TX_Only_Simplex_Unidirect_Master
PB13.Signal=SPI2_SCK
PB15.Mode=TX_Only_Simplex_Unidirect_Master
PB15.Signal=SPI2_MOSI
PB3.GPIOParameters=GPIO_Label
PB3.GPIO_Label=CE
PB3.Signal=GPIO_Output
PB4.GPIOParameters=GPIO_Label
PB4.GPIO_Label=PL
PB4.Signal=GPIO_Output
PB6.Mode=I2C
PB6.Signal=I2C1_SCL
PB7.Mode=I2C
PB7.Signal=I2C1_SDA
PD0-OSC_IN.Mode=HSE-External-Oscillator
PD0-OSC_IN.Signal=RCC_OSC_IN
PD1-OSC_OUT.Mode=HSE-External-Oscillator
PD1-OSC_OUT.Signal=RCC_OSC_OUT
RCC.SYSCLKFreq_VALUE=72000000
RCC.SYSCLKSource=RCC_SYSCLKSOURCE_PLLCLK
board=custom

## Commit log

2025-05-08 initial
2025-06-17 create PCB && Software
2025-06-18 Completed the schematic drawing, started the PCB process, and updated the firmware to the helloword firmware.
2025-06-19 complete layout
2025-06-20 start generic cabling
2025-06-25 Update the PCB layout
2025-06-26 complete Key line
2025-06-26 Complete the non-power line routing
2025-06-27 change the keyboard
2025-06-28 complete desin
2025-06-29 complete all
2025-08-03 last up
